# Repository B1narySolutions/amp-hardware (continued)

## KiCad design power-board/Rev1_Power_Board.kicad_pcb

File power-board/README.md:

# Power board

The power board's KiCad project, rev 1 (`Rev1_Power_Board.kicad_pro`).

## What the audio board needs from it

The audio board (`../audio-board/rev2/`) connects through two screw terminals, six wires in all. This is the contract
between the two boards; `../audio-board/rev2/DESIGN.md` gives the reasons ("Power board connector (J6)", "Output mute",
"Speaker send", "Display connector (J3)", "What each connector can see"). If the power board departs from a number here,
change it here and in that DESIGN.md together, and review both boards against the new number.

| Signal | Driven by | Promise |
|---|---|---|
| 5V (J6.1) | Power board | 4.75–5.25 V (5.0 V ± 5 %), never above 5.5 V |
| BAT (J6.3) | Power board | 0–3.3 V, source impedance 10 kΩ or less |
| MUTE (J6.4) | Power board pulls up, audio board pulls down | Pull-up of 4.7 kΩ or more to at most the 5 V rail; the audio board pulls it to ≈ 0.24–0.5 V to play |
| LINE+ (J5.1) | Audio board | Audio, full scale ≈ 1 Vrms (1.5 V peak), ≈ 0 V DC, from ≈ 1 kΩ (at most 1.1 kΩ) |
| LINE− (J5.2) | Audio board | The audio board's ground through ≈ 1 kΩ (0 V ± 10 mV) |
| LINE+ / LINE− load | Power board | 10 kΩ–1 MΩ per leg |

### Connections
J6 (4-way) and J5 (2-way) are 3.5 mm screw terminals on the audio board. Seen from the wire side, J6 reads 5V, GND, BAT,
MUTE from left to right (pins 1–4); J5 is 1 LINE+, 2 LINE−. The audio board's J3 (GND, TX, RX) is the UART to the
display, not a power board connection.

### 5 V supply (J6.1, J6.2)
- 4.75–5.25 V at J6, never above 5.5 V: the audio board's op-amp and headphone amp run straight from it. Its firmware
  won't start audio below 4.7 V or keep it running below 4.4 V.
- The audio board draws well under 1 A (the Daisy roughly 100–200 mA). One 5 V wire and one GND wire.
- The audio board has reverse-polarity protection (Q1), but nothing else on the power board should rely on it.

### Power switch and battery
- **The battery:** a Talentcell power bank, "72W 100Wh 12V/8300mAh 9V/11000mAh 5V/20000mAh"
  ([eBay listing](https://www.ebay.com/itm/278396464326)), a finished pack with its own charger and protection. The
  power board takes its 12 V output. The listing doesn't say whether that is regulated, so assume 9.0 V empty to 12.6 V
  full, measure it, and fuse the input.
- **Put the power switch and the low-battery cutoff on the power board.** The audio board can't turn the power off, and
  its firmware assumes the power can disappear at any time.
- **Battery level (J6.3, BAT):** a voltage proportional to the battery, scaled to 0–3.3 V, from 10 kΩ or less. The audio
  board loads it with 20 kΩ (R13 + R22) and reads V × 10k / (20k + R_source). Rev 1 uses 30k over 10k: a ratio of 0.25
  (3.15 V at 12.6 V) from 7.5 kΩ. Record the ratio and source impedance in the audio board's DESIGN.md. Switch the
  divider off with the 5 V, so it doesn't drain the battery.

### Speaker amp
- **Input (J5):** wire LINE+ to the amp's IN+ and LINE− to its IN− **only**, never to the amp's GND as well. LINE− is the
  audio board's ground through 1 kΩ, so the amp rejects any voltage between the two boards' grounds; tied to the amp's
  GND it would close a ground loop through J6 and J5.
- **Input impedance:** 10 kΩ or more per leg. The audio board drives each leg through 1 kΩ, so full scale arrives at
  ≈ 0.83 Vrms differential into 10 kΩ (−1.7 dB), and ≈ 3.0 dB lower into 5 kΩ. J5 should sit at ≈ 0 V DC (the audio
  board's TEST_PLAN 5.16).
- **Mute (J6.4):** the audio board pulls MUTE to GND through Q2 and 470 Ω to play, and leaves it open to mute. Pull it up
  with 4.7 kΩ or more to at most 5 V, so the amp is muted whenever the audio board is unpowered, booting, reset or
  unplugged. Low is ≈ 0.24 V against 10 kΩ and ≈ 0.5 V against 4.7 kΩ; the amp has to read that as "play".
- **The speakers:** 10" 4 Ω cones, one at a time. Neither speaker wire may be grounded (the output is bridged).
  - Jensen MOD10-50, 4 Ω ([Amplified Parts](https://www.amplifiedparts.com/products/speaker-jensen-mod-10-mod10-50-50w)):
    50 W, ≈ 95 dB at 1 W / 1 m, 3.08 Ω DC (distributor figures). Roughly 105–107 dB at 1 m from the amp's ≈ 17 W.
  - Skar Audio FSX10-4 ([eBay listing](https://www.ebay.com/itm/187823581724)), a "flat" pro-audio midrange: 400 W, no
    sensitivity or response figures.

#### The amp: TI TPA3118D2
How the TPA3118D2 (datasheet SLOS708G) meets each point:
- **Mute:** MUTE is active high with TTL levels, so `SPK_MUTE` wires straight to it with the pull-up above. Its levels
  follow AVCC, which is always above 5 V here. Use SDZ (active low) for the power board's own sequencing.
- **Input:** fully differential, each leg through its own coupling cap of the same type and value (the datasheet
  suggests 1.5 µF at 20 dB).
- **Gain: 20 dB, the lowest setting.** Input impedance falls from 60 kΩ at 20 dB to 9 kΩ at 36 dB, ±20 %, so 36 dB
  breaks the 10 kΩ-per-leg minimum. Full scale (≈ 0.98 Vrms after the 1 kΩ legs into 60 kΩ) becomes ≈ 9.8 Vrms, which
  already clips on the battery: ≈ 1.5 dB below full scale on a full pack, ≈ 2.5 dB at 11.1 V, ≈ 4.5 dB near 9 V. The
  firmware caps the speaker level about 5 dB below full scale.
- **Supply:** 4.5–26 V, straight from the 12 V output.
- **Output:** both channels in PBTL for the single speaker. Into 4 Ω, roughly 17 W at clipping on a full pack, 13 W at
  11.1 V and 9 W near 9 V (allowing ≈ 0.3 Ω for the switches and inductors), drawing up to ≈ 1.6 A on loud peaks.
- **Package:** HTSSOP-32 with a thermal pad. Lay the pad out with vias that can be soldered from the back, or use hot air.

### Display
Supply the display's 5 V directly from the power board, on its own wire pair, so its current pulses (Wi-Fi, backlight
PWM) never flow through the audio board's `+5V`.

### Wiring and placement
- Use ferrules or solid wire in the screw terminals. Tinned stranded wire creeps and loosens.
- Run J5 as a short twisted pair, away from the guitar input and the speaker wires.
- Keep the regulators and class D amp away from the audio board's analog circuits.
- The audio board survives 5 V landing on BAT or MUTE, and probably on LINE+ (≈ 3 mA into the codec output's
  protection). Check every wire against the silkscreen before powering up anyway.

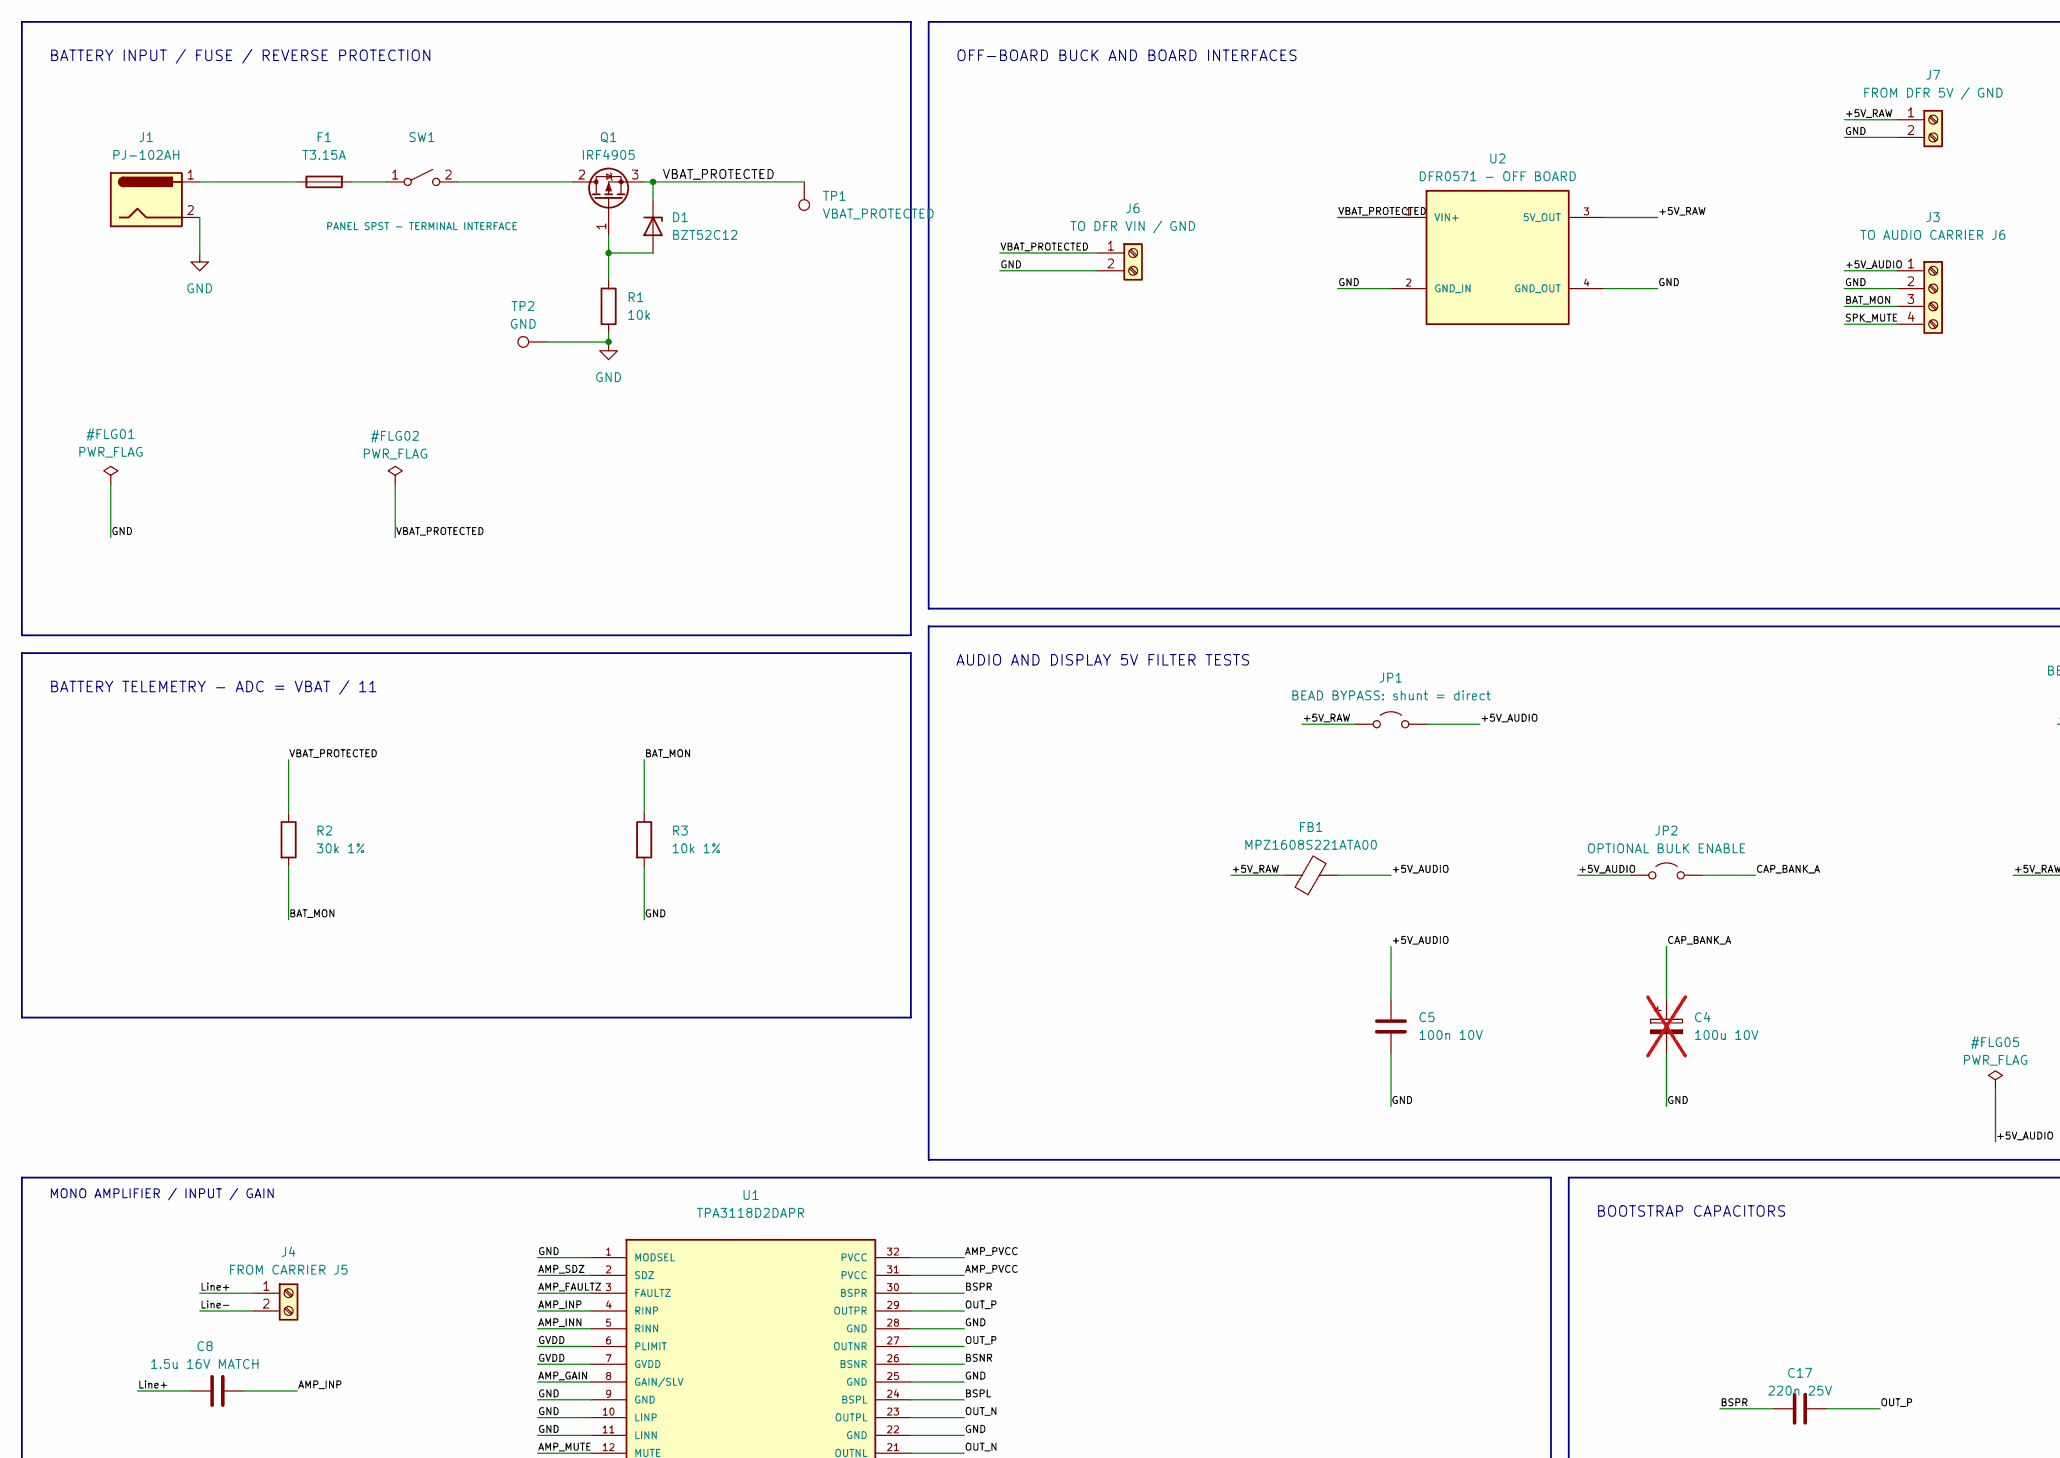
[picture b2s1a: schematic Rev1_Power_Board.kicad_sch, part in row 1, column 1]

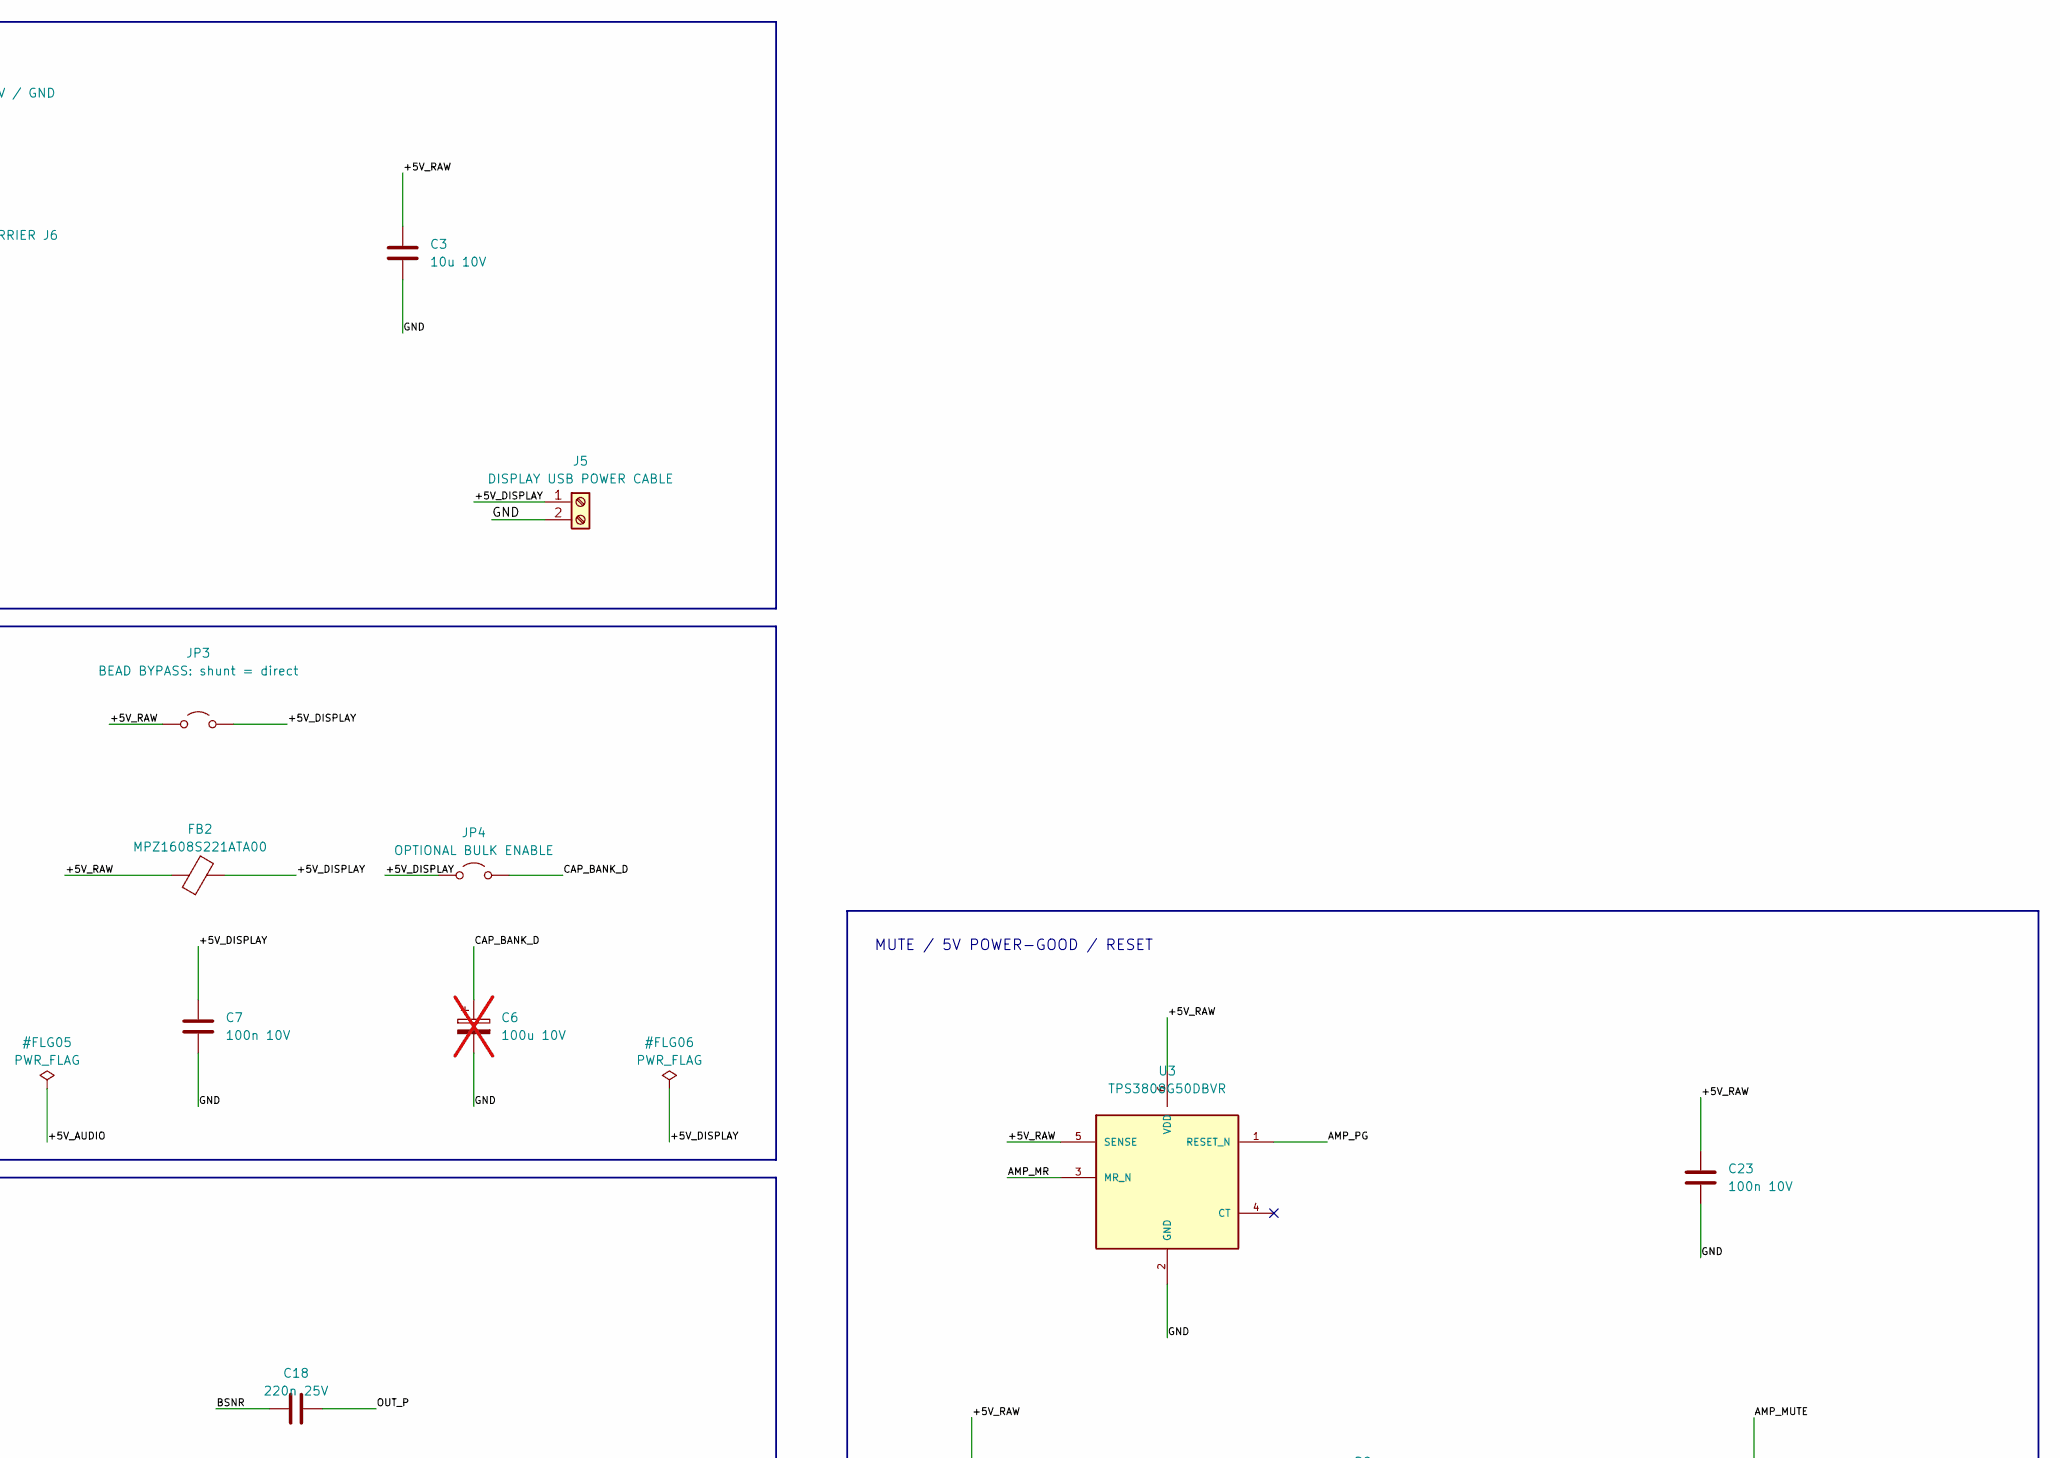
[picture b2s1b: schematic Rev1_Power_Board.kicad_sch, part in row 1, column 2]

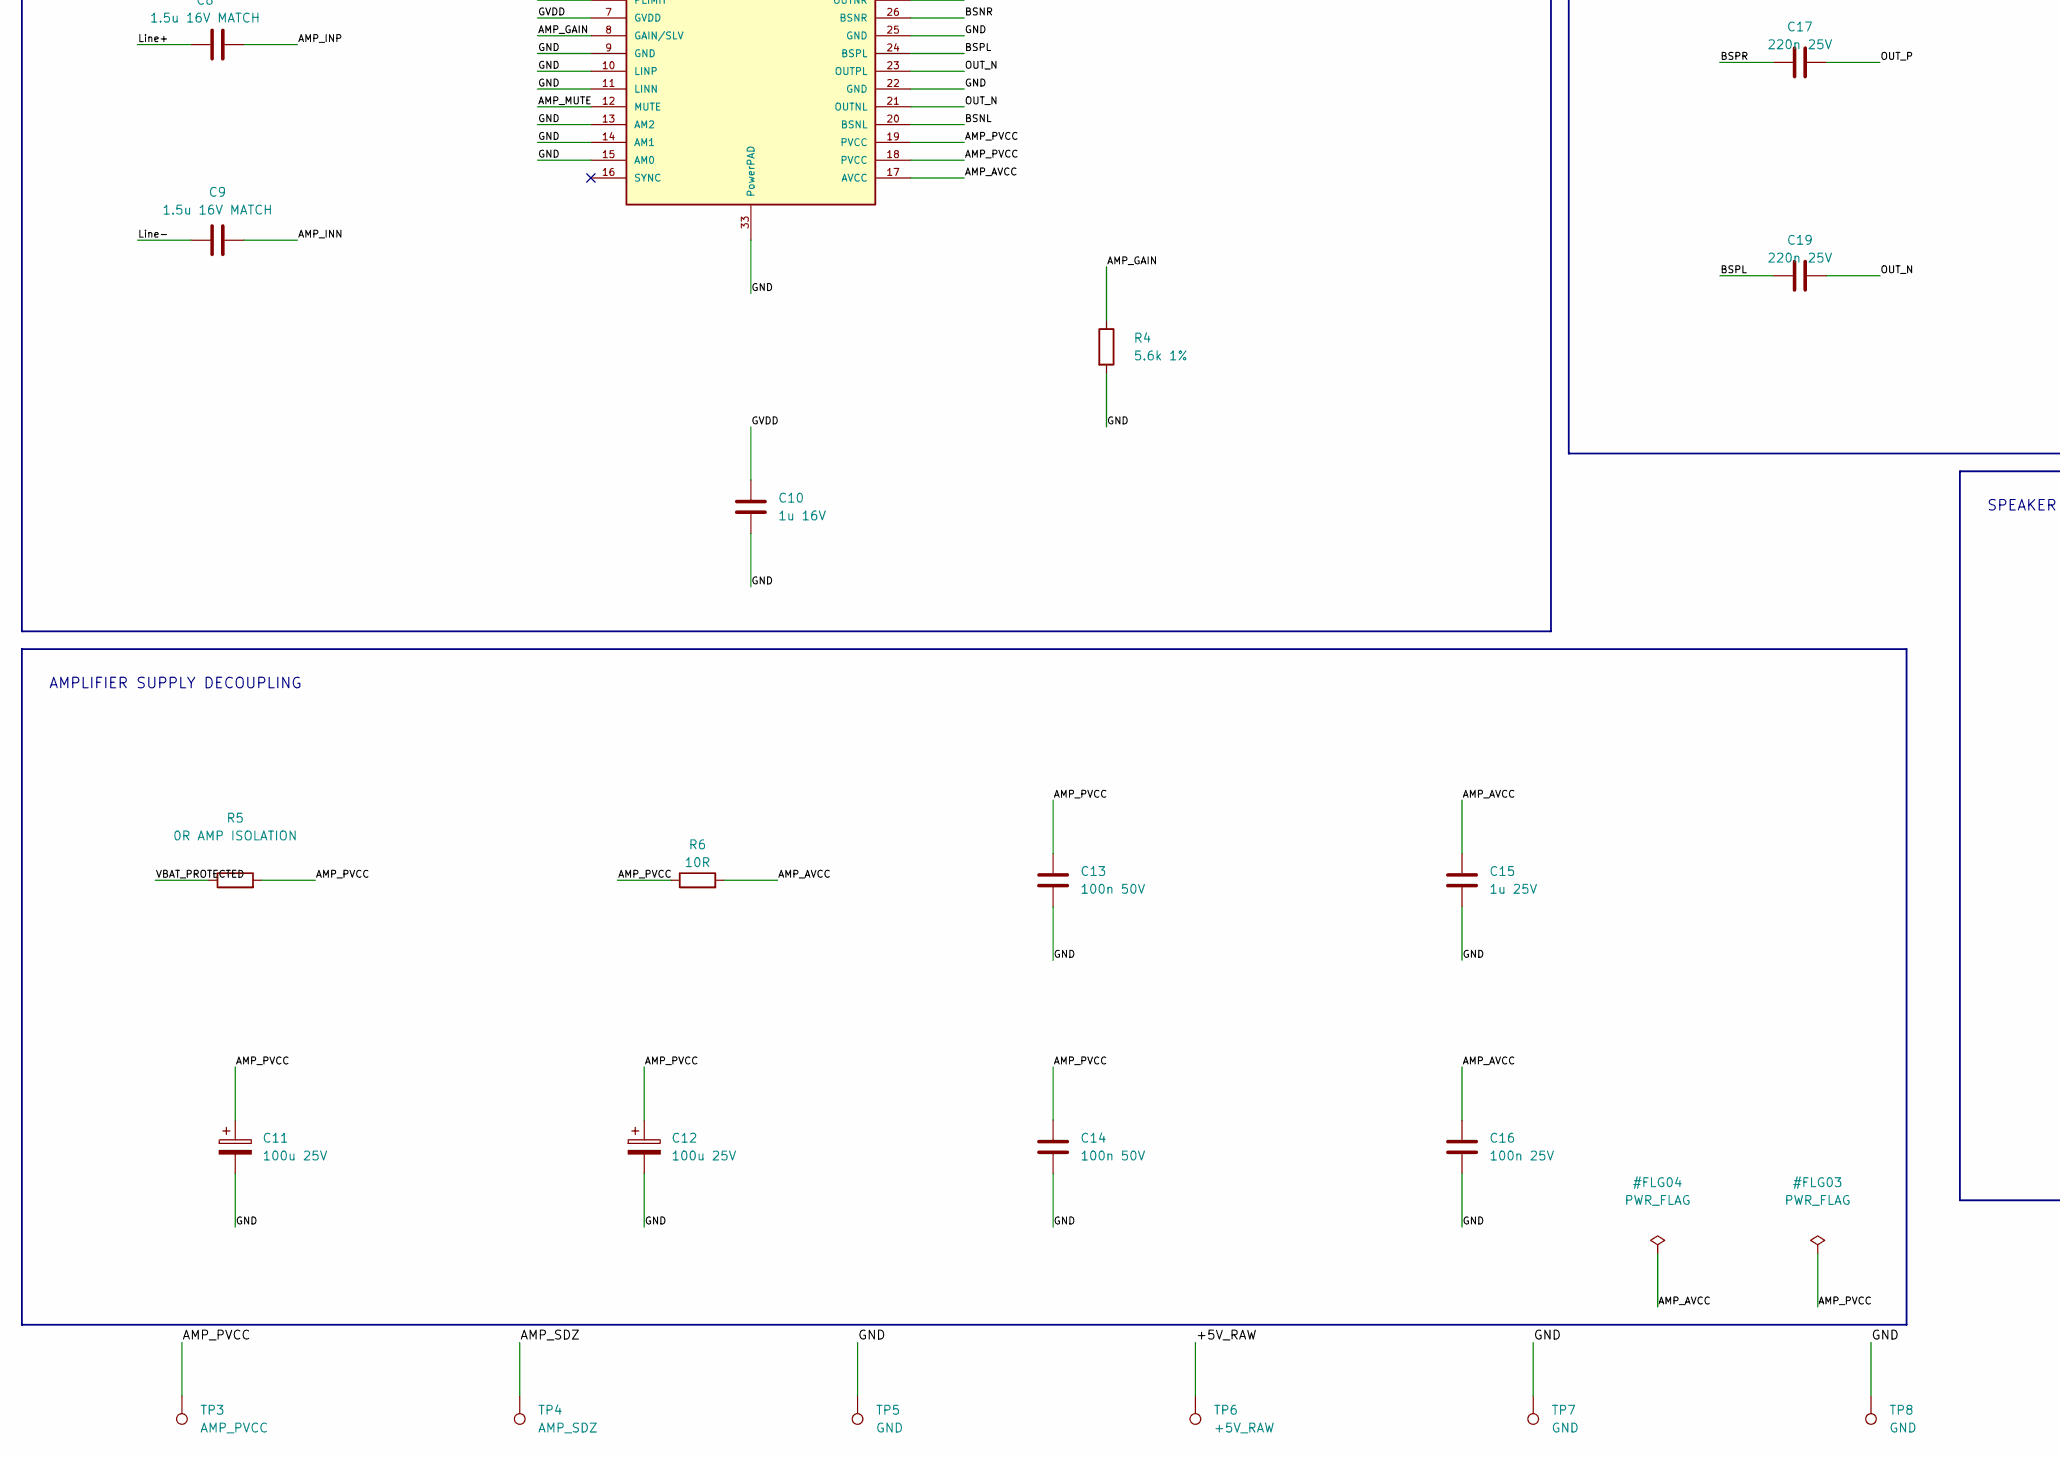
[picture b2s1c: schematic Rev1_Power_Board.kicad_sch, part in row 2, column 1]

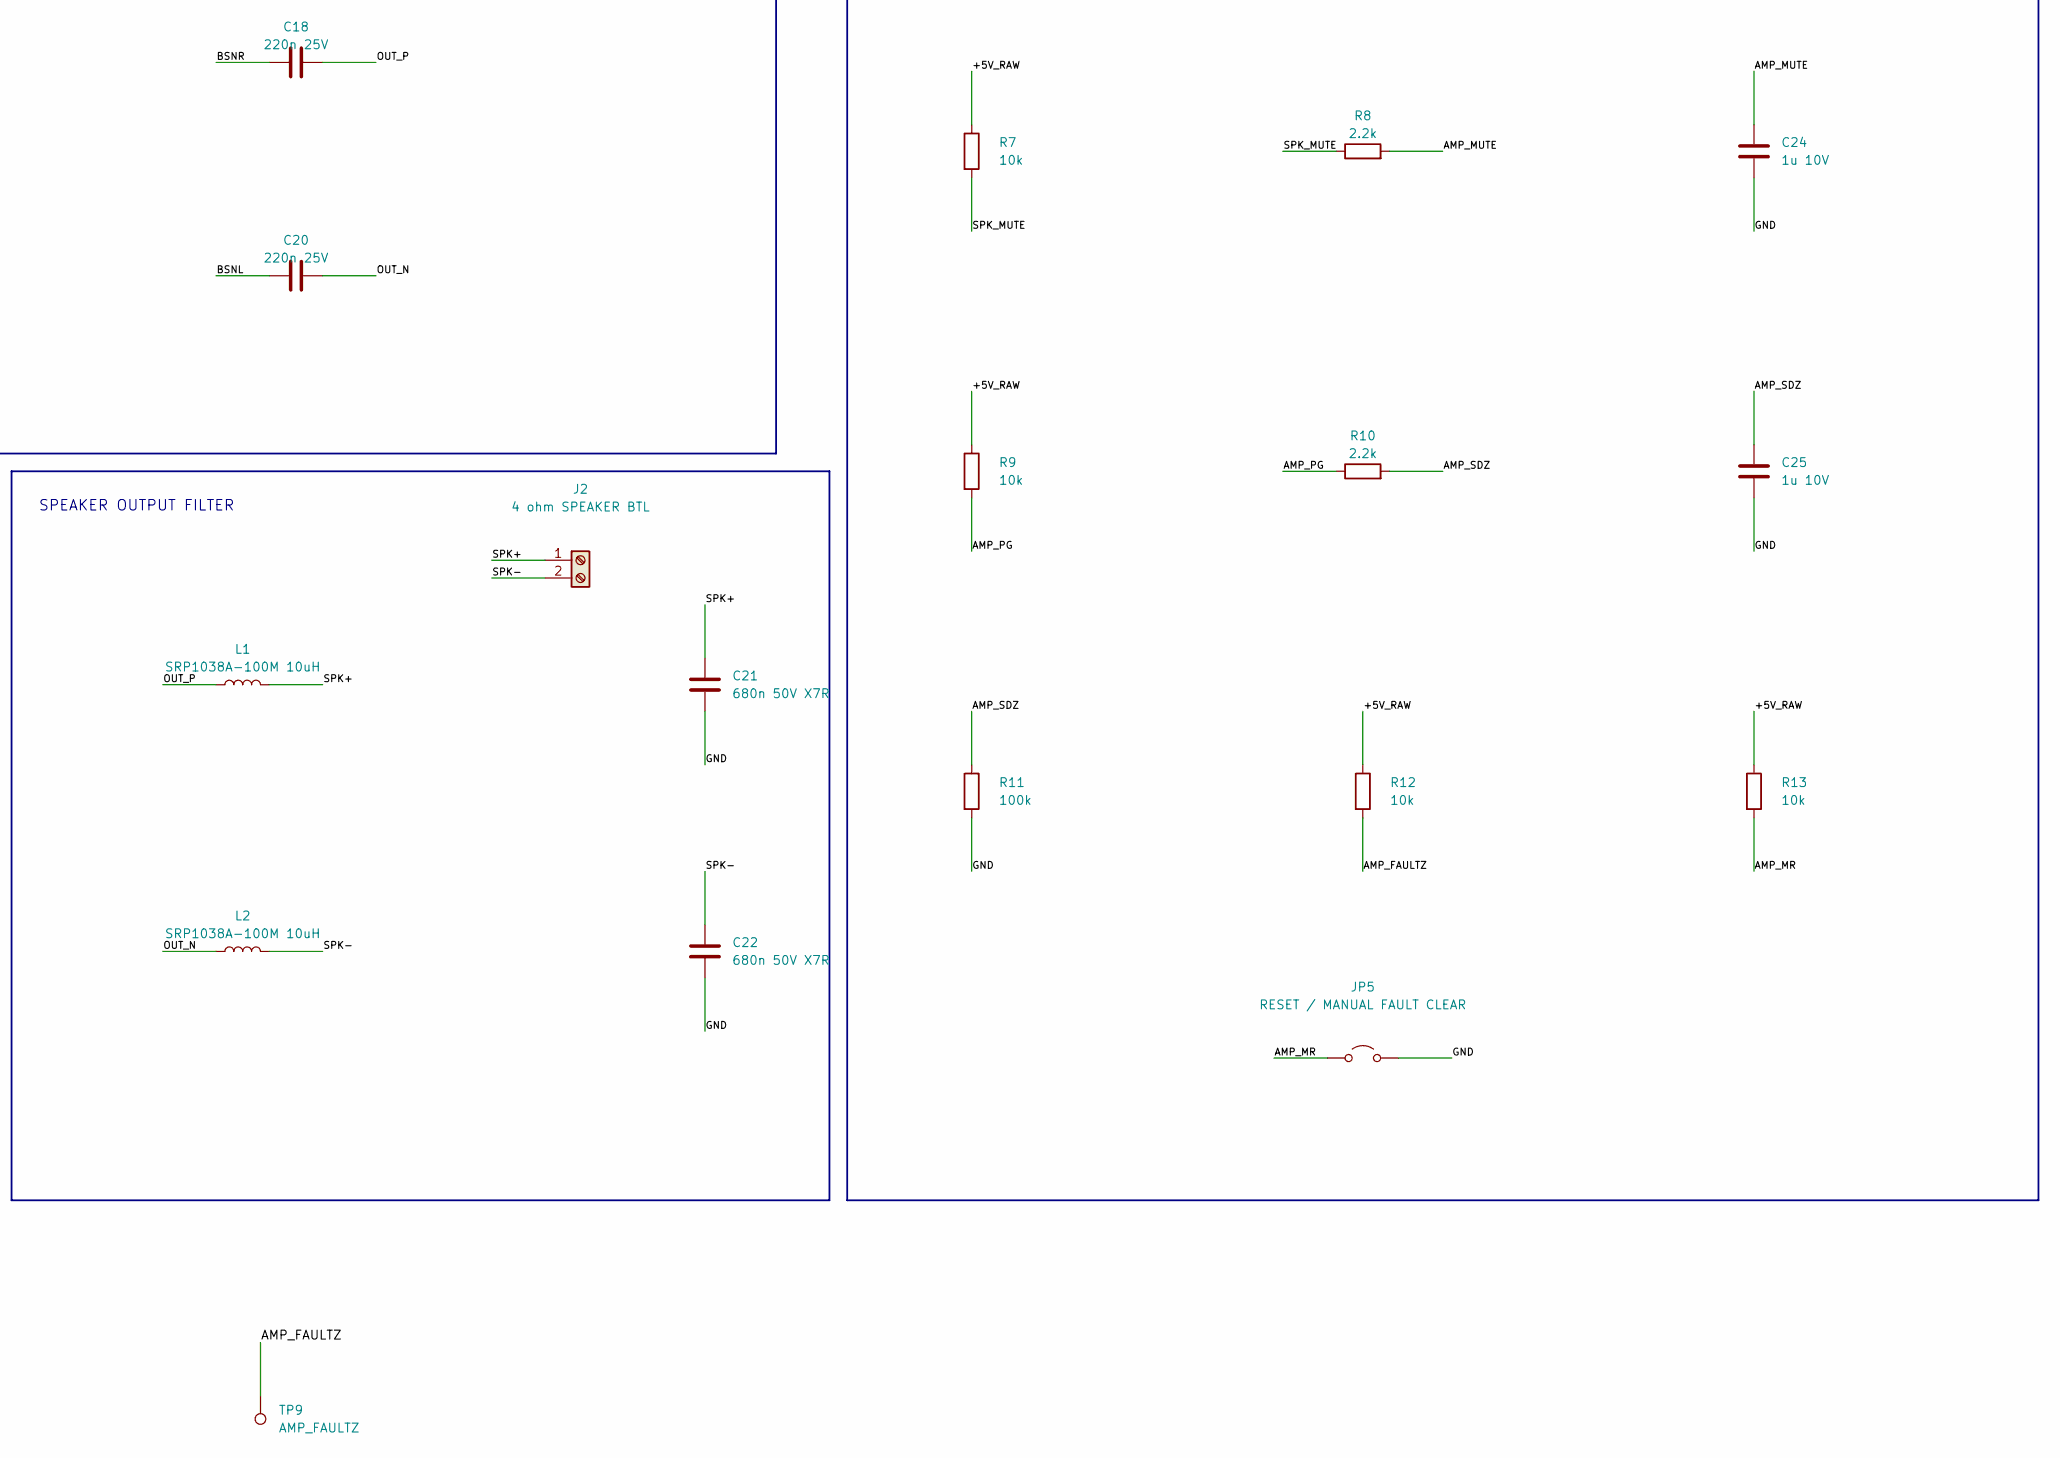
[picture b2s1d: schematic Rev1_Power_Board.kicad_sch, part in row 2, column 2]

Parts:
C3: 10u 10V; C_1206_3216Metric_Pad1.33x1.80mm_HandSolder; MPN C1206C106K4RACTU
C4, C6: 100u 10V; CP_Radial_D6.3mm_P2.50mm; MPN EEU-FR1E101; not fitted
C5, C7, C23: 100n 10V; C_1206_3216Metric_Pad1.33x1.80mm_HandSolder; MPN C1206C104K5RACTU
C8, C9: 1.5u 16V MATCH; C_1206_3216Metric_Pad1.33x1.80mm_HandSolder; MPN GRM31MR71E155KA88L
C10: 1u 16V; C_0805_2012Metric; MPN C0805C105K5RACTU
C11, C12: 100u 25V; CP_Radial_D6.3mm_P2.50mm; MPN EEU-FR1E101
C13, C14: 100n 50V; C_0805_2012Metric; MPN C0805C104K5RACTU
C15: 1u 25V; C_1206_3216Metric_Pad1.33x1.80mm_HandSolder; MPN C1206C105K5RACTU
C16: 100n 25V; C_0805_2012Metric; MPN C0805C104K5RACTU
C17, C18, C19, C20: 220n 25V; C_0805_2012Metric; MPN C0805C224K3RACTU
C21, C22: 680n 50V X7R; C_1206_3216Metric_Pad1.33x1.80mm_HandSolder; MPN C1206C684K5RACTU
C24, C25: 1u 10V; C_1206_3216Metric_Pad1.33x1.80mm_HandSolder; MPN C1206C105K5RACTU
D1: BZT52C12; D_SOD-123; MPN BZT52C12-7-F
F1: T3.15A; Fuseholder_Bulgin_FX0457_P10.00mm; MPN FX0457
FB1, FB2: MPZ1608S221ATA00; L_0603_1608Metric; MPN MPZ1608S221ATA00
J1: PJ-102AH; BarrelJack_CUI_PJ-102AH_Horizontal; MPN PJ-102AH; DigiKey CP-102AH-ND
J2: 4 ohm SPEAKER BTL; TerminalBlock_Phoenix_PT-1,5-2-3.5-H_1x02_P3.50mm_Horizontal; MPN 1984617
J3: TO AUDIO CARRIER J6; TerminalBlock_Phoenix_PT-1,5-4-3.5-H_1x04_P3.50mm_Horizontal; MPN 1984633
J4: FROM CARRIER J5; TerminalBlock_Phoenix_PT-1,5-2-3.5-H_1x02_P3.50mm_Horizontal; MPN 1984617
J5: DISPLAY USB POWER CABLE; TerminalBlock_Phoenix_PT-1,5-2-3.5-H_1x02_P3.50mm_Horizontal; MPN 1984617
J6: TO DFR VIN / GND; TerminalBlock_Phoenix_PT-1,5-2-3.5-H_1x02_P3.50mm_Horizontal; MPN 1984617
J7: FROM DFR 5V / GND; TerminalBlock_Phoenix_PT-1,5-2-3.5-H_1x02_P3.50mm_Horizontal; MPN 1984617
JP1, JP3: BEAD BYPASS: shunt = direct; PinHeader_1x02_P2.54mm_Vertical; MPN M20-9990245
JP2, JP4: OPTIONAL BULK ENABLE; PinHeader_1x02_P2.54mm_Vertical; MPN M20-9990245
JP5: RESET / MANUAL FAULT CLEAR; PinHeader_1x02_P2.54mm_Vertical; MPN M20-9990245
L1, L2: SRP1038A-100M 10uH; L_Bourns_SRP1038A_LeadFrame; MPN SRP1038A-100M
Q1: IRF4905; TO-220-3_Vertical; MPN IRF4905PBF
R1, R7, R9, R12, R13: 10k; R_1206_3216Metric_Pad1.30x1.75mm_HandSolder; MPN RC1206FR-0710KL
R2: 30k 1%; R_1206_3216Metric_Pad1.30x1.75mm_HandSolder; MPN RC1206FR-0730KL
R3: 10k 1%; R_1206_3216Metric_Pad1.30x1.75mm_HandSolder; MPN RC1206FR-0710KL
R4: 5.6k 1%; R_1206_3216Metric_Pad1.30x1.75mm_HandSolder; MPN RC1206FR-075K6L
R5: 0R AMP ISOLATION; R_2512_6332Metric; MPN RC2512JK-070RL
R6: 10R; R_1206_3216Metric_Pad1.30x1.75mm_HandSolder; MPN RC1206FR-0710RL
R8, R10: 2.2k; R_1206_3216Metric_Pad1.30x1.75mm_HandSolder; MPN RC1206FR-072K2L
R11: 100k; R_1206_3216Metric_Pad1.30x1.75mm_HandSolder; MPN RC1206FR-07100KL
SW1: PANEL SPST - TERMINAL INTERFACE; TerminalBlock_Phoenix_PT-1,5-2-3.5-H_1x02_P3.50mm_Horizontal; MPN 1984617
TP1: VBAT_PROTECTED; TestPoint_Pad_D2.0mm
TP2, TP5, TP7, TP8: GND; TestPoint_Pad_D2.0mm
TP3: AMP_PVCC; TestPoint_Pad_D2.0mm
TP4: AMP_SDZ; TestPoint_Pad_D2.0mm
TP6: +5V_RAW; TestPoint_Pad_D2.0mm
TP9: AMP_FAULTZ; TestPoint_Pad_D2.0mm
U1: TPA3118D2DAPR; TI_DAP0032C_HTSSOP32_P0.65mm_EP3.04x3.74mm; MPN TPA3118D2DAPR
U2: DFR0571 - OFF BOARD
U3: TPS3808G50DBVR; SOT-23-6; MPN TPS3808G50DBVR

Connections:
/+5V_AUDIO: C5.1, FB1.2, J3.1, JP1.2 (B), JP2.1 (A)
/+5V_DISPLAY: C7.1, FB2.2, J5.1, JP3.2 (B), JP4.1 (A)
/+5V_RAW: C3.1, C23.1, FB1.1, FB2.1, J7.1, JP1.1 (A), JP3.1 (A), R7.1, R9.1, R12.1, R13.1, TP6.1 (1_1), U2.3 (5V_OUT), U3.5 (SENSE), U3.6 (VDD)
/AMP_AVCC: C15.1, C16.1, R6.2, U1.17 (AVCC)
/AMP_FAULTZ: R12.2, TP9.1, U1.3 (FAULTZ)
/AMP_GAIN: R4.1, U1.8 (GAIN/SLV)
/AMP_INN: C9.2, U1.5 (RINN)
/AMP_INP: C8.2, U1.4 (RINP)
/AMP_MR: JP5.1 (A), R13.2, U3.3 (MR_N)
/AMP_MUTE: C24.1, R8.2, U1.12 (MUTE)
/AMP_PG: R9.2, R10.1, U3.1 (RESET_N)
/AMP_PVCC: C11.1, C12.1, C13.1, C14.1, R5.2, R6.1, TP3.1 (1_1), U1.18 (PVCC), U1.19 (PVCC), U1.31 (PVCC), U1.32 (PVCC)
/AMP_SDZ: C25.1, R10.2, R11.1, TP4.1 (1_1), U1.2 (SDZ)
/BAT_MON: J3.3, R2.2, R3.1
/BSNL: C20.1, U1.20 (BSNL)
/BSNR: C18.1, U1.26 (BSNR)
/BSPL: C19.1, U1.24 (BSPL)
/BSPR: C17.1, U1.30 (BSPR)
/CAP_BANK_A: C4.1, JP2.2 (B)
/CAP_BANK_D: C6.1, JP4.2 (B)
/GVDD: C10.1, U1.6 (PLIMIT), U1.7 (GVDD)
/Line+: C8.1, J4.1
/Line-: C9.1, J4.2
/OUT_N: C19.2, C20.2, L2.1, U1.21 (OUTNL), U1.23 (OUTPL)
/OUT_P: C17.2, C18.2, L1.1, U1.27 (OUTNR), U1.29 (OUTPR)
/SPK+: C21.1, J2.1, L1.2
/SPK-: C22.1, J2.2, L2.2
/SPK_MUTE: J3.4, R7.2, R8.1
/VBAT_PROTECTED: D1.1 (K), J6.1, Q1.3 (S), R2.1, R5.1, TP1.1, U2.1 (VIN+); also elsewhere on the board
GND: C3.2, C4.2, C5.2, C6.2, C7.2, C10.2, C11.2, C12.2, C13.2, C14.2, C15.2, C16.2, C21.2, C22.2, C23.2, C24.2, C25.2, J1.2, J3.2, J5.2, J6.2, J7.2, JP5.2 (B), R1.2, R3.2, R4.2, R11.2, TP2.1 (1_1), TP5.1, TP7.1 (1_1), TP8.1 (1_1), U1.1 (MODSEL), U1.9 (GND), U1.10 (LINP), U1.11 (LINN), U1.13 (AM2), U1.14 (AM1), U1.15 (AM0), U1.22 (GND), U1.25 (GND), U1.28 (GND), U1.33 (PowerPAD), U2.2 (GND_IN), U2.4 (GND_OUT), U3.2 (GND); also elsewhere on the board
unnamed: D1.2 (A), Q1.1 (G), R1.1
unnamed: F1.1, J1.1
unnamed: Q1.2 (D), SW1.2 (B)
unnamed: F1.2, SW1.1 (A)

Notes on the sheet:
OFF-BOARD BUCK AND BOARD INTERFACES
BOOTSTRAP CAPACITORS
MONO AMPLIFIER / INPUT / GAIN
AUDIO AND DISPLAY 5V FILTER TESTS
BATTERY INPUT / FUSE / REVERSE PROTECTION
AMPLIFIER SUPPLY DECOUPLING
SPEAKER OUTPUT FILTER
MUTE / 5V POWER-GOOD / RESET
BATTERY TELEMETRY - ADC = VBAT / 11

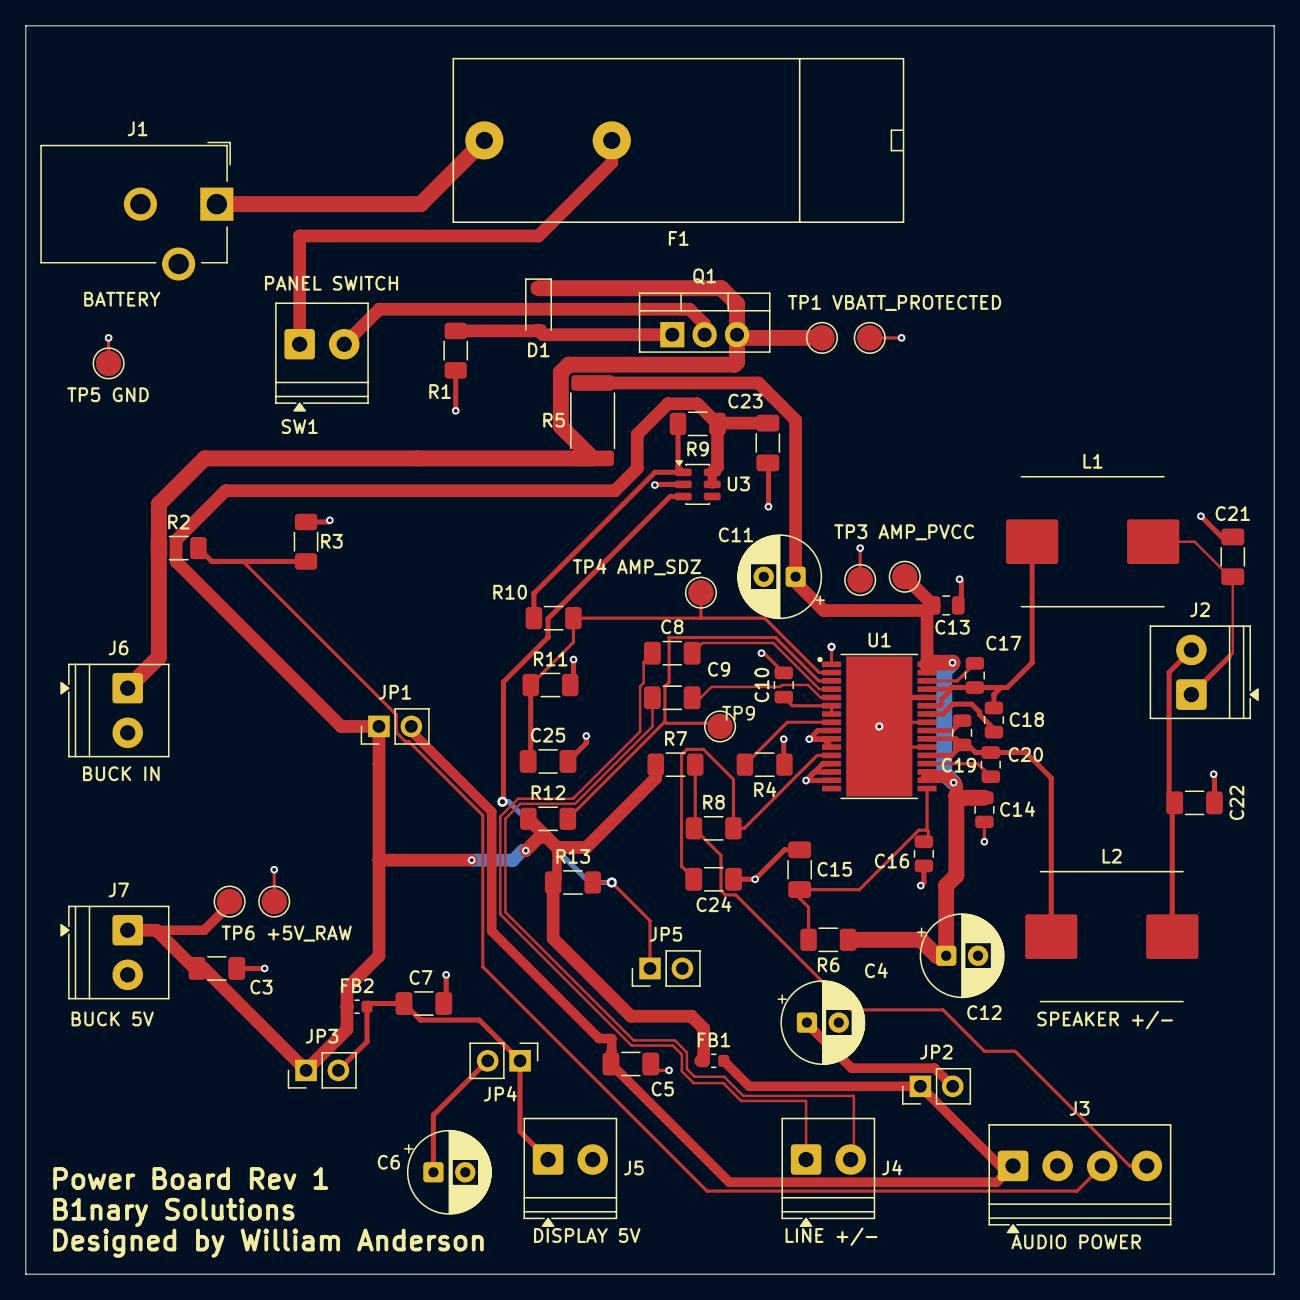
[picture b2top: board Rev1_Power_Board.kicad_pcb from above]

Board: 2 copper layers, 98.0 x 98.0 mm, 67 parts (0 on the bottom side), 34 nets.

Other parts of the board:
TP1 VBATT_PROTECTED: VBAT_PROTECTED; TestPoint_Pad_D2.0mm
TP5 GND: GND; TestPoint_Pad_D2.0mm

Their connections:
/VBAT_PROTECTED: TP1 VBATT_PROTECTED.1 (1_1); also elsewhere on the board
GND: TP5 GND.1 (1_1); also elsewhere on the board
